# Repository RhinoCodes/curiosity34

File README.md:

# Curiosity34

This keyboard is inspired by the reviung 34 by @gtips. In fact, it uses the exact same layout. The main features of this board are:
* Integrated
* USB-C Through C3 Daughterboard

A GB will be running with this design and a custom milled POM case in colaboration with Glow#2411 on Discord.
Join [Glow's discord](https://discord.gg/yF7jkNbdqk) for updates

Contact: sudo killall windows#0042

## Pictures

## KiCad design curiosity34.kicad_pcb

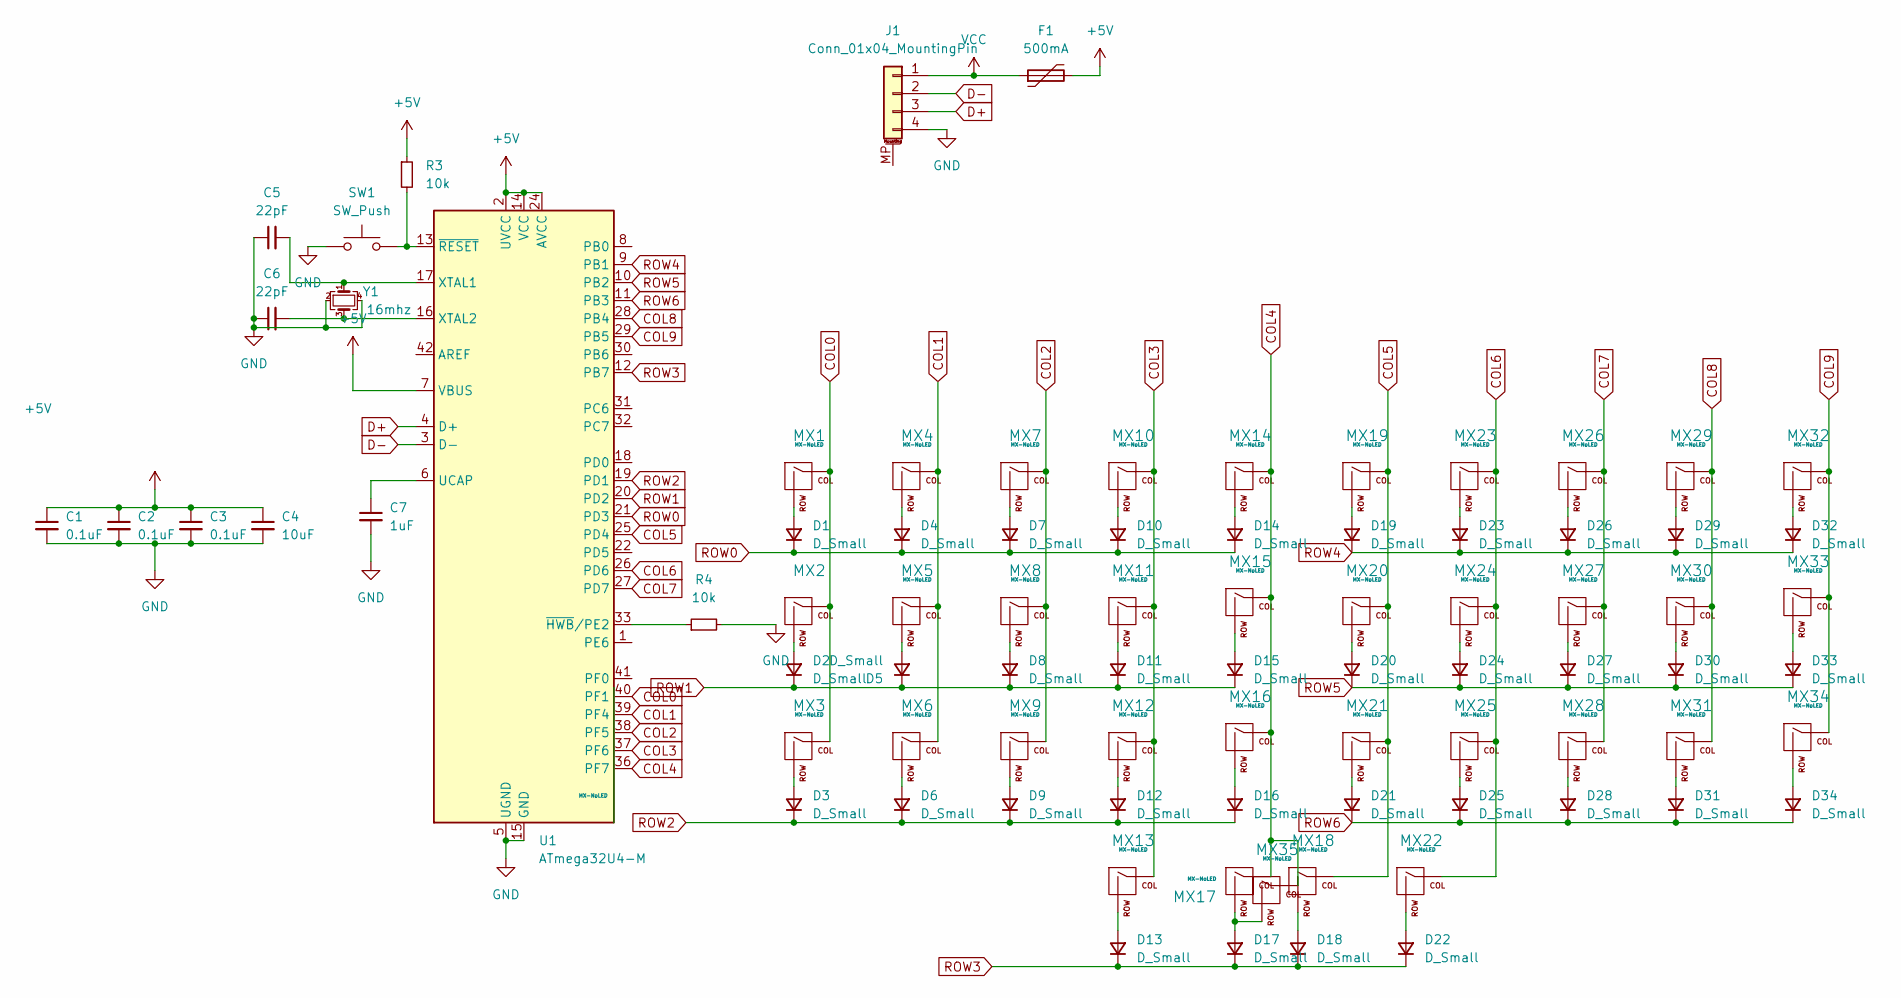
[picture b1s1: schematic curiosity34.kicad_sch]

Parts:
C1, C2, C3: 0.1uF; C_0805_2012Metric
C4: 10uF; C_0805_2012Metric
C5, C6: 22pF; C_0805_2012Metric
C7: 1uF; C_0805_2012Metric
D1, D2, D3, D4, D5, D6, D7, D8, D9, D10, D11, D12, D13, D14, D15, D16, D17, D18, D19, D20, D21, D22, D23, D24, D25, D26, D27, D28, D29, D30, D31, D32, D33, D34: D_Small; D_SOD-123
F1: 500mA; Fuse_1206_3216Metric
J1: Conn_01x04_MountingPin; JST-SR-4
MX1, MX2, MX3, MX4, MX5, MX6, MX7, MX8, MX9, MX10, MX11, MX12, MX13, MX14, MX15, MX16, MX17, MX18, MX19, MX20, MX21, MX22, MX23, MX24, MX25, MX26, MX27, MX28, MX29, MX30, MX31, MX32, MX33, MX34, MX35: MX-NoLED; MX-1U-NoLED
R3, R4: 10k; R_0805_2012Metric
SW1: SW_Push; SKQG-1155865
U1: ATmega32U4-M; QFN-44-1EP_7x7mm_P0.5mm_EP5.2x5.2mm
Y1: 16mhz; Crystal_SMD_3225-4Pin_3.2x2.5mm

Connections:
+5V: C1.1, C2.1, C3.1, C4.1, F1.2, R3.1, U1.2 (UVCC), U1.7 (VBUS), U1.14 (VCC), U1.24 (AVCC), U1.34 (VCC), U1.44 (AVCC)
COL0: MX1.1 (COL), MX2.1 (COL), MX3.1 (COL), U1.40 (PF1)
COL1: MX4.1 (COL), MX5.1 (COL), MX6.1 (COL), U1.39 (PF4)
COL2: MX7.1 (COL), MX8.1 (COL), MX9.1 (COL), U1.38 (PF5)
COL3: MX10.1 (COL), MX11.1 (COL), MX12.1 (COL), MX13.1 (COL), U1.37 (PF6)
COL4: MX14.1 (COL), MX15.1 (COL), MX16.1 (COL), MX17.1 (COL), MX35.1 (COL), U1.36 (PF7)
COL5: MX18.1 (COL), MX19.1 (COL), MX20.1 (COL), MX21.1 (COL), U1.25 (PD4)
COL6: MX22.1 (COL), MX23.1 (COL), MX24.1 (COL), MX25.1 (COL), U1.26 (PD6)
COL7: MX26.1 (COL), MX27.1 (COL), MX28.1 (COL), U1.27 (PD7)
COL8: MX29.1 (COL), MX30.1 (COL), MX31.1 (COL), U1.28 (PB4)
COL9: MX32.1 (COL), MX33.1 (COL), MX34.1 (COL), U1.29 (PB5)
D+: J1.3, U1.4 (D+)
D-: J1.2, U1.3 (D-)
GND: C1.2, C2.2, C3.2, C4.2, C5.1, C6.1, C7.2, J1.4, R4.2, SW1.1, U1.5 (UGND), U1.15 (GND), U1.23 (GND), U1.35 (GND), U1.43 (GND), U1.45 (GND), Y1.2, Y1.4
unnamed: C5.2, U1.17 (XTAL1), Y1.1
unnamed: C6.2, U1.16 (XTAL2), Y1.3
unnamed: C7.1, U1.6 (UCAP)
unnamed: D6.2 (A), MX6.2 (ROW)
unnamed: D12.2 (A), MX12.2 (ROW)
unnamed: D13.2 (A), MX13.2 (ROW)
unnamed: D15.2 (A), MX15.2 (ROW)
unnamed: D23.2 (A), MX23.2 (ROW)
unnamed: D1.2 (A), MX1.2 (ROW)
unnamed: D2.2 (A), MX2.2 (ROW)
unnamed: D3.2 (A), MX3.2 (ROW)
unnamed: D4.2 (A), MX4.2 (ROW)
unnamed: D5.2 (A), MX5.2 (ROW)
unnamed: D7.2 (A), MX7.2 (ROW)
unnamed: D8.2 (A), MX8.2 (ROW)
unnamed: D9.2 (A), MX9.2 (ROW)
unnamed: D10.2 (A), MX10.2 (ROW)
unnamed: D11.2 (A), MX11.2 (ROW)
unnamed: D14.2 (A), MX14.2 (ROW)
unnamed: D16.2 (A), MX16.2 (ROW)
unnamed: D17.2 (A), MX17.2 (ROW), MX35.2 (ROW)
unnamed: D18.2 (A), MX18.2 (ROW)
unnamed: D19.2 (A), MX19.2 (ROW)
unnamed: D20.2 (A), MX20.2 (ROW)
unnamed: D21.2 (A), MX21.2 (ROW)
unnamed: D22.2 (A), MX22.2 (ROW)
unnamed: D24.2 (A), MX24.2 (ROW)
unnamed: D25.2 (A), MX25.2 (ROW)
unnamed: D26.2 (A), MX26.2 (ROW)
unnamed: D27.2 (A), MX27.2 (ROW)
unnamed: D28.2 (A), MX28.2 (ROW)
unnamed: D29.2 (A), MX29.2 (ROW)
unnamed: D30.2 (A), MX30.2 (ROW)
unnamed: D31.2 (A), MX31.2 (ROW)
unnamed: D32.2 (A), MX32.2 (ROW)
unnamed: D33.2 (A), MX33.2 (ROW)
unnamed: D34.2 (A), MX34.2 (ROW)
unnamed: R3.2, SW1.2, U1.13 (~RESET)
unnamed: R4.1, U1.33 (~HWB/PE2)
ROW0: D1.1 (K), D4.1 (K), D7.1 (K), D10.1 (K), D14.1 (K), U1.21 (PD3)
ROW1: D2.1 (K), D5.1 (K), D8.1 (K), D11.1 (K), D15.1 (K), U1.20 (PD2)
ROW2: D3.1 (K), D6.1 (K), D9.1 (K), D12.1 (K), D16.1 (K), U1.19 (PD1)
ROW3: D13.1 (K), D17.1 (K), D18.1 (K), D22.1 (K), U1.12 (PB7)
ROW4: D19.1 (K), D23.1 (K), D26.1 (K), D29.1 (K), D32.1 (K), U1.9 (PB1)
ROW5: D20.1 (K), D24.1 (K), D27.1 (K), D30.1 (K), D33.1 (K), U1.10 (PB2)
ROW6: D21.1 (K), D25.1 (K), D28.1 (K), D31.1 (K), D34.1 (K), U1.11 (PB3)
VCC: F1.1, J1.1

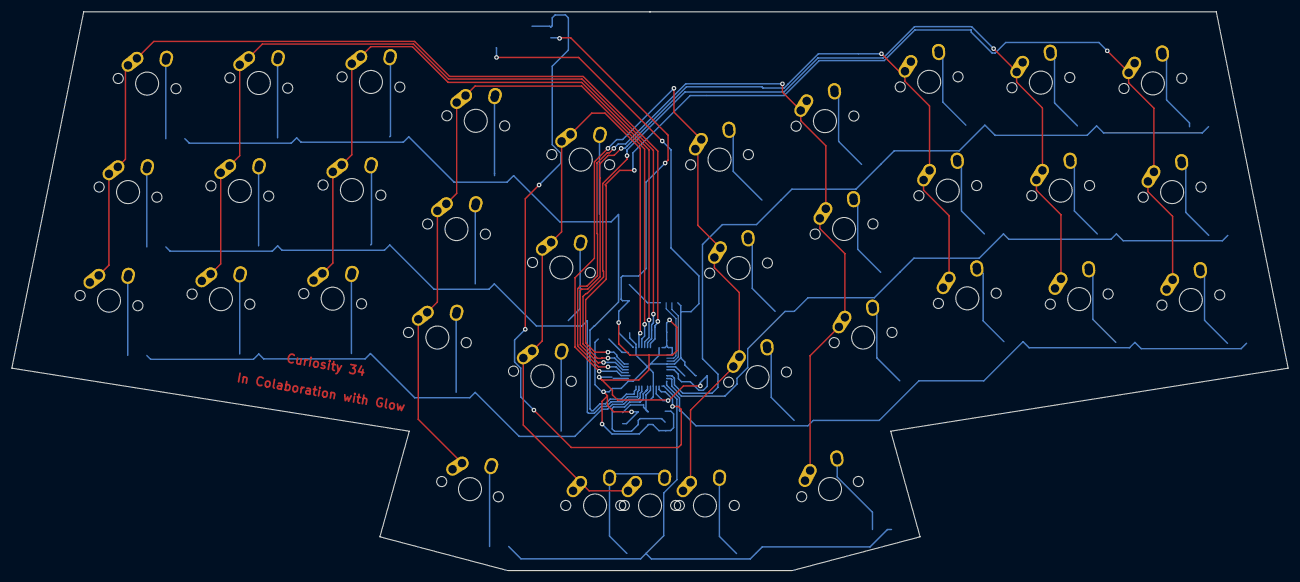
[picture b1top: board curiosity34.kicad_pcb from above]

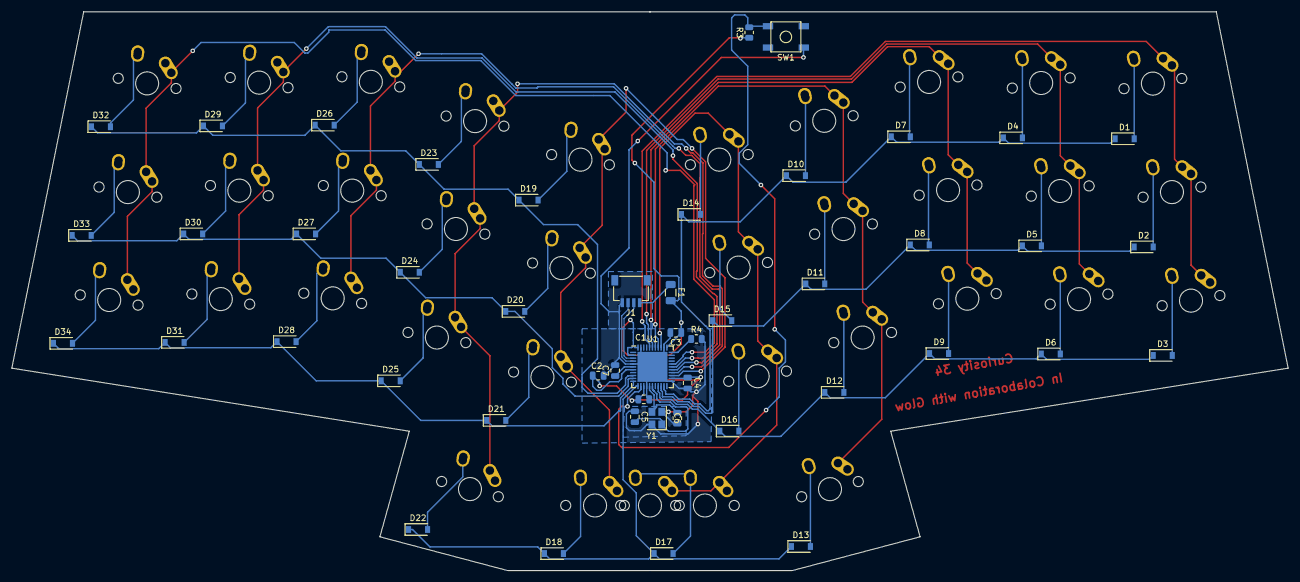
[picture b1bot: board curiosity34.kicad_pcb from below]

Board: 2 copper layers, 221.1 x 96.8 mm, 83 parts (48 on the bottom side), 61 nets.

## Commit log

2022-01-18 Add README
2022-01-18 Fix images
